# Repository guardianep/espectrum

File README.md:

# Spectre Audio Mixer

A USB audio mixer PCB with per-app volume control. Link any three applications to physical sliders and control their volume on the fly without tabbing out.

## Features

- Link any three apps to individual volume sliders
- Seamless app-to-slider mapping via desktop controller
- LED level indicators (1-10) showing current volume per slider
- OLED display showing active app mappings
- Reactive LED indicators synced to system volume
- Works in games without alt-tabbing

## Hardware Design

KiCad files available in `hardware/kicad/`:
- Schematic: `Spectre.kicad_sch`
- PCB Layout: `Spectre.kicad_pcb`

**Microcontroller:**
- ESP32-C3-DevKitM-1

**Sensors & Controls:**
- 3x Potentiometer sliders (10kΩ)
- GPIO pins 3, 4, 5 for analog input

**Output:**
- 30x SK6812MINI-E addressable RGB LEDs (10 per slider)
- SSD1306 OLED display (128x64) via I2C
- 5V and 3.3V power rails with 220µF decoupling capacitor
- 360Ω series resistors on LED data lines

**Power:**
- USB-C (5V from ESP32)
- Separate 5V rail for LEDs, 3.3V for logic

## Software

**Desktop Controller (Python):**
- Tkinter GUI for app selection
- Serial communication at 115200 baud
- Sends config format: `S1:Chrome|S2:Spotify|S3:Discord`

**Firmware (ESP32-C3):**
- Arduino framework with PlatformIO
- Adafruit NeoPixel library for LED control
- Adafruit SSD1306 library for OLED display
- Serial parsing for configuration updates

## Setup

### Hardware Assembly
1. Solder SK6812MINI-E LEDs to GPIO 0, 1, 2 (10 each)
2. Connect potentiometers to GPIO 3, 4, 5
3. Wire SSD1306 OLED via I2C (SDA, SCL)
4. Add 220µF capacitor across 5V/GND rails
5. Add 360Ω resistors on LED data lines

### Firmware
1. Install PlatformIO
2. Build and upload to ESP32-C3
3. Connect via USB (COM3 on Windows)

### Desktop App
```bash
pip install pyserial psutil
python spectre_controller.py
```

## Usage

1. Run desktop controller
2. Select apps from dropdown menus (Slider 1, 2, 3)
3. Click "Save Configuration"
4. OLED displays active app mappings
5. Move sliders to control individual app volumes
6. LED bars show volume level (1-10 LEDs lit)

## Status

- Firmware: Complete (Steps 1-4 done)
- Desktop Controller: BETA (app selection refinement in progress)
- Hardware: PCB designed, awaiting fabrication

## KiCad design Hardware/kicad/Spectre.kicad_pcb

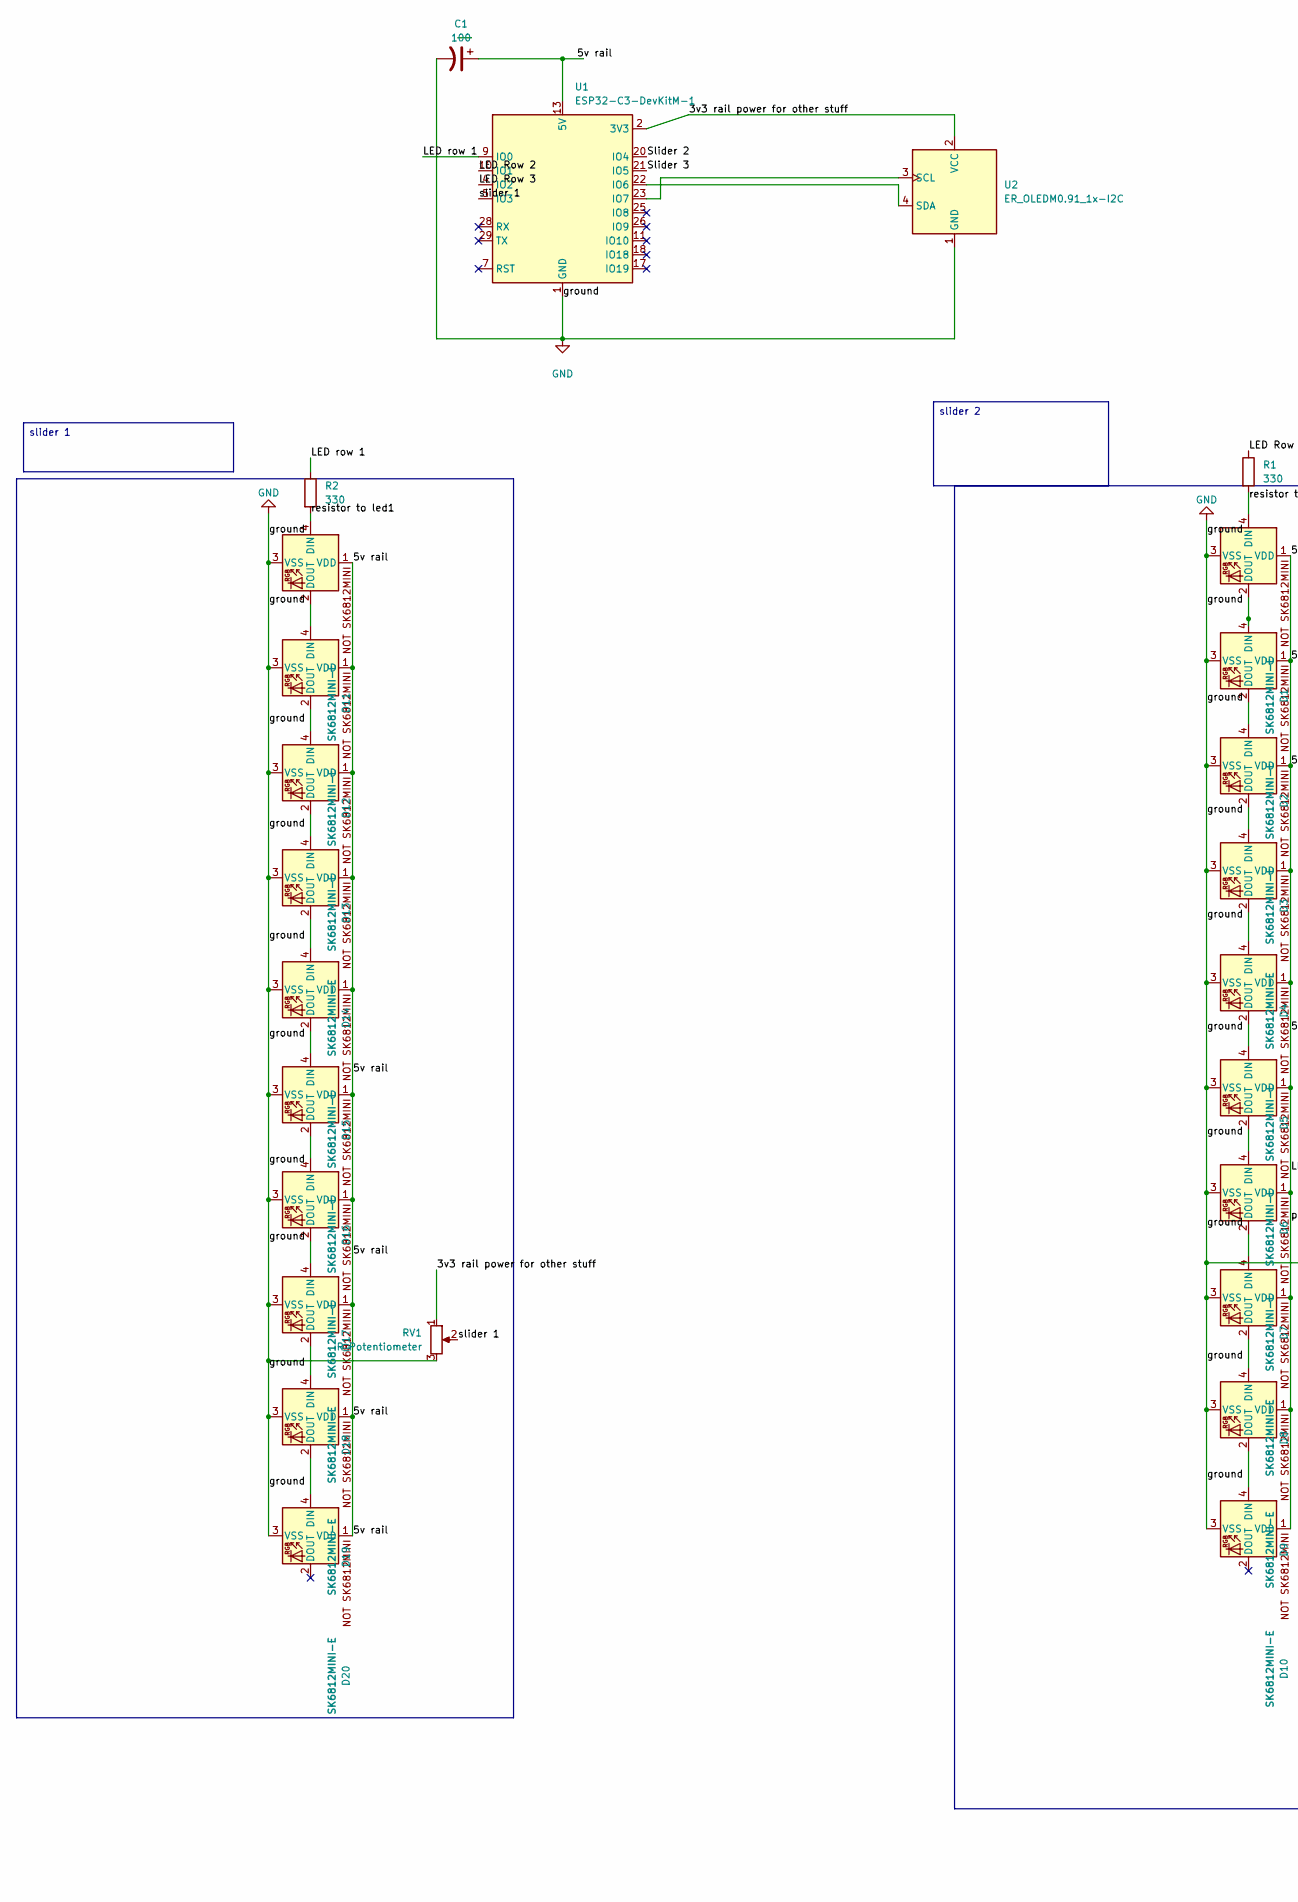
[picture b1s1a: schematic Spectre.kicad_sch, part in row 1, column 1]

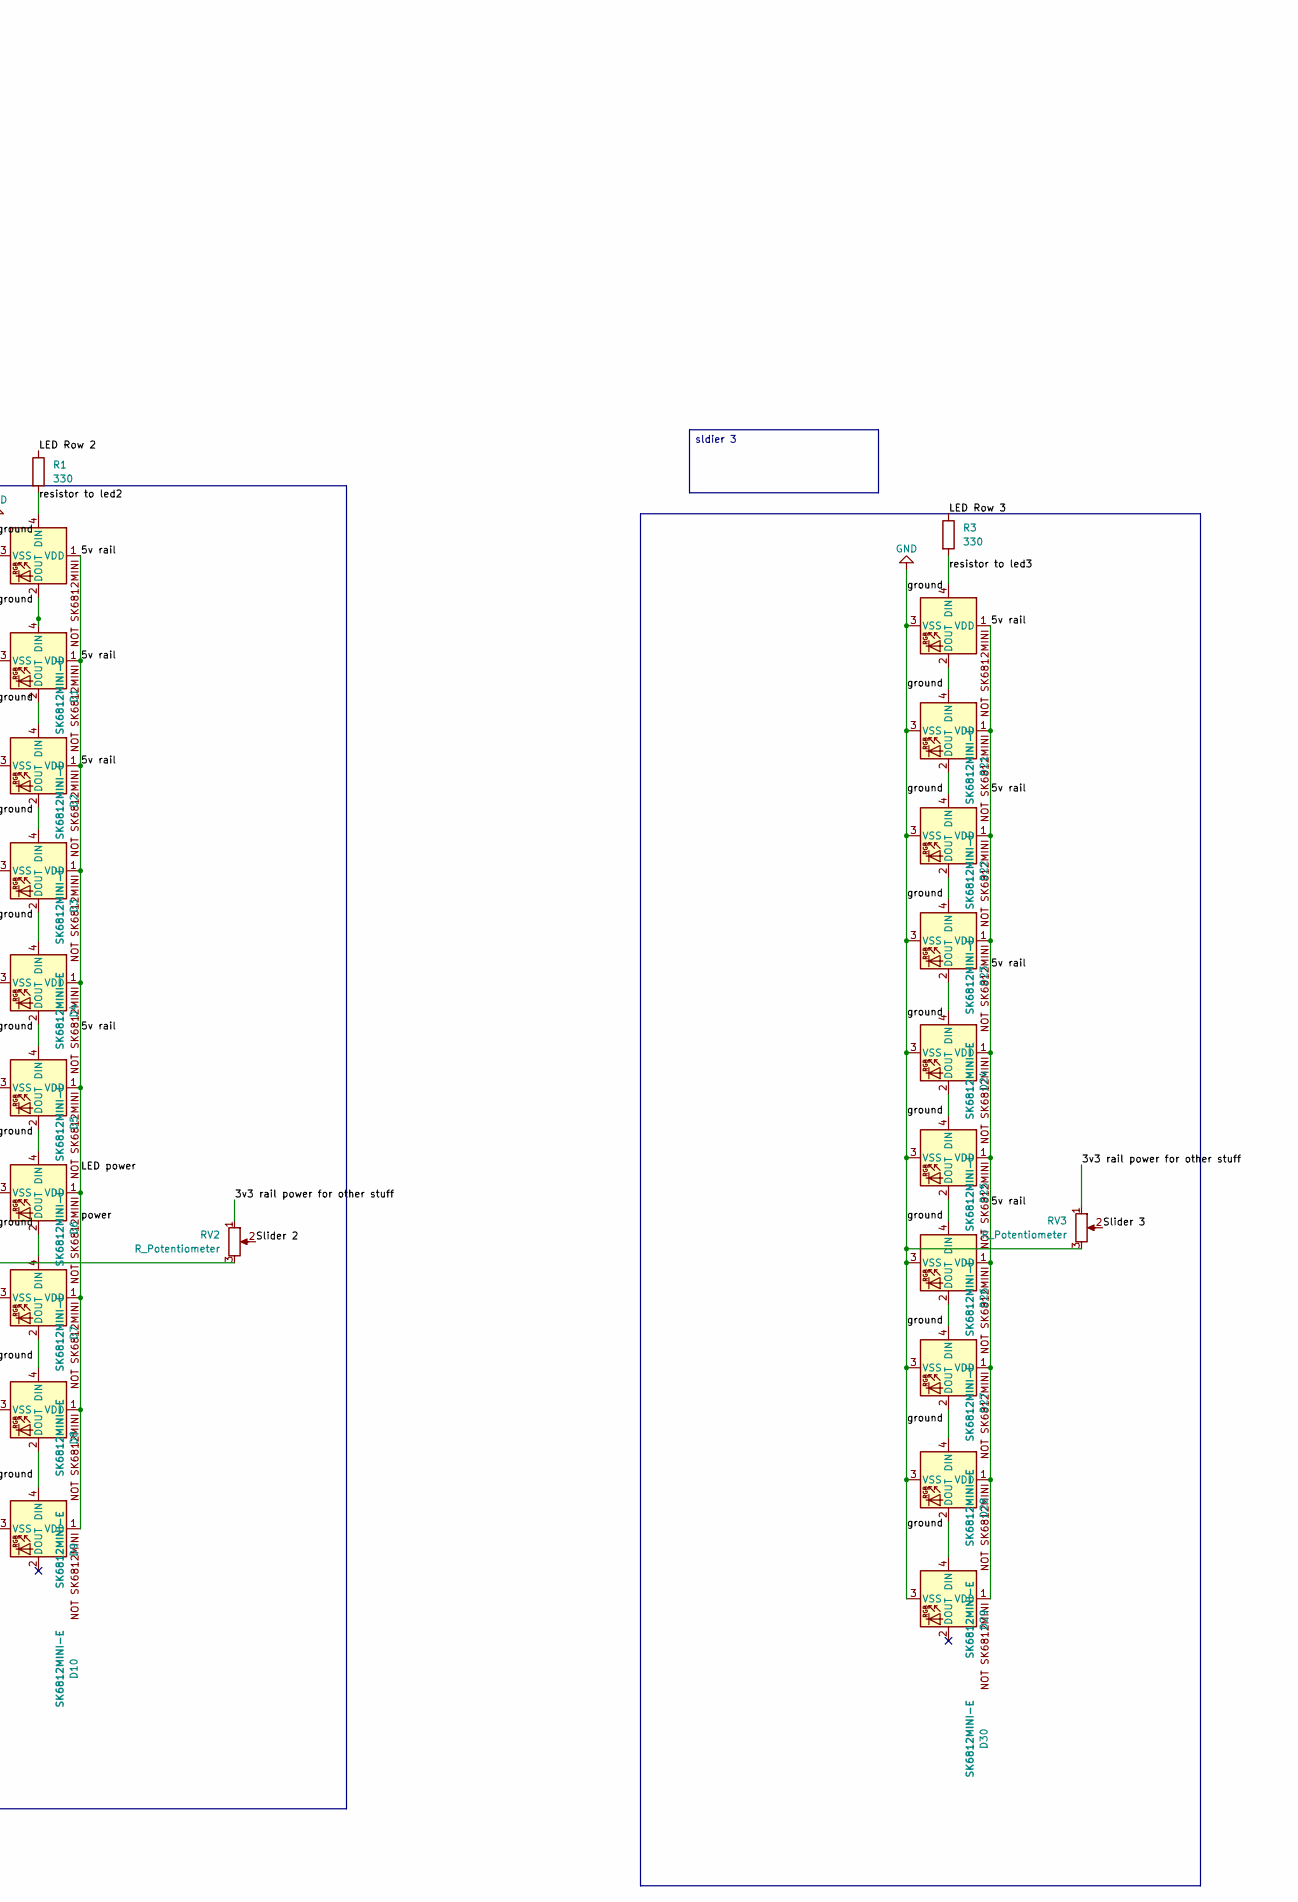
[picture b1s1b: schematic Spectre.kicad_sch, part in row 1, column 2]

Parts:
C1: 100; CP_Radial_D5.0mm_P2.00mm
D1, D2, D3, D4, D5, D6, D7, D8, D9, D10, D11, D12, D13, D14, D15, D16, D17, D18, D19, D20, D21, D22, D23, D24, D25, D26, D27, D28, D29, D30: SK6812MINI-E; SK6812MINI-E_fixed_fixed
R1, R2, R3: 330; R_Axial_DIN0207_L6.3mm_D2.5mm_P2.54mm_Vertical
RV1, RV2, RV3: R_Potentiometer; Potentiometer_Bourns_PTA3043_Single_Slide
U1: ESP32-C3-DevKitM-1; ESP32-C3-DevKitM-1-3
U2: ER_OLEDM0.91_1x-I2C; ER_OLEDM0.91_1x-I2C-new-newser

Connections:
/3v3 rail power for other stuff: RV1.1, RV2.1, RV3.1, U1.2 (3V3), U1.3 (3V3), U2.2 (VCC)
/5v rail: C1.1, D1.1 (VDD), D2.1 (VDD), D3.1 (VDD), D4.1 (VDD), D5.1 (VDD), D6.1 (VDD), D7.1 (VDD), D8.1 (VDD), D9.1 (VDD), D10.1 (VDD), D11.1 (VDD), D12.1 (VDD), D13.1 (VDD), D14.1 (VDD), D15.1 (VDD), D16.1 (VDD), D17.1 (VDD), D18.1 (VDD), D19.1 (VDD), D20.1 (VDD), D21.1 (VDD), D22.1 (VDD), D23.1 (VDD), D24.1 (VDD), D25.1 (VDD), D26.1 (VDD), D27.1 (VDD), D28.1 (VDD), D29.1 (VDD), D30.1 (VDD), U1.13 (5V), U1.14 (5V)
/LED Row 2: R1.1, U1.10 (IO1)
/LED Row 3: R3.1, U1.4 (IO2)
/LED row 1: R2.1, U1.9 (IO0)
/Slider 2: RV2.2, U1.20 (IO4)
/Slider 3: RV3.2, U1.21 (IO5)
/resistor to led1: D11.4 (DIN), R2.2
/resistor to led2: D1.4 (DIN), R1.2
/resistor to led3: D21.4 (DIN), R3.2
/slider 1: RV1.2, U1.5 (IO3)
GND: C1.2, D1.3 (VSS), D2.3 (VSS), D3.3 (VSS), D4.3 (VSS), D5.3 (VSS), D6.3 (VSS), D7.3 (VSS), D8.3 (VSS), D9.3 (VSS), D10.3 (VSS), D11.3 (VSS), D12.3 (VSS), D13.3 (VSS), D14.3 (VSS), D15.3 (VSS), D16.3 (VSS), D17.3 (VSS), D18.3 (VSS), D19.3 (VSS), D20.3 (VSS), D21.3 (VSS), D22.3 (VSS), D23.3 (VSS), D24.3 (VSS), D25.3 (VSS), D26.3 (VSS), D27.3 (VSS), D28.3 (VSS), D29.3 (VSS), D30.3 (VSS), RV1.3, RV2.3, RV3.3, U1.1 (GND), U1.6 (GND), U1.8 (GND), U1.12 (GND), U1.15 (GND), U1.16 (GND), U1.19 (GND), U1.24 (GND), U1.27 (GND), U1.30 (GND), U2.1 (GND)
unnamed: D1.2 (DOUT), D2.4 (DIN)
unnamed: D2.2 (DOUT), D3.4 (DIN)
unnamed: D3.2 (DOUT), D4.4 (DIN)
unnamed: D4.2 (DOUT), D5.4 (DIN)
unnamed: D5.2 (DOUT), D6.4 (DIN)
unnamed: D6.2 (DOUT), D7.4 (DIN)
unnamed: D7.2 (DOUT), D8.4 (DIN)
unnamed: D8.2 (DOUT), D9.4 (DIN)
unnamed: D9.2 (DOUT), D10.4 (DIN)
unnamed: D11.2 (DOUT), D12.4 (DIN)
unnamed: D12.2 (DOUT), D13.4 (DIN)
unnamed: D13.2 (DOUT), D14.4 (DIN)
unnamed: D14.2 (DOUT), D15.4 (DIN)
unnamed: D15.2 (DOUT), D16.4 (DIN)
unnamed: D16.2 (DOUT), D17.4 (DIN)
unnamed: D17.2 (DOUT), D18.4 (DIN)
unnamed: D18.2 (DOUT), D19.4 (DIN)
unnamed: D19.2 (DOUT), D20.4 (DIN)
unnamed: D21.2 (DOUT), D22.4 (DIN)
unnamed: D22.2 (DOUT), D23.4 (DIN)
unnamed: D23.2 (DOUT), D24.4 (DIN)
unnamed: D24.2 (DOUT), D25.4 (DIN)
unnamed: D25.2 (DOUT), D26.4 (DIN)
unnamed: D26.2 (DOUT), D27.4 (DIN)
unnamed: D27.2 (DOUT), D28.4 (DIN)
unnamed: D28.2 (DOUT), D29.4 (DIN)
unnamed: D29.2 (DOUT), D30.4 (DIN)
unnamed: U1.22 (IO6), U2.4 (SDA)
unnamed: U1.23 (IO7), U2.3 (SCL)

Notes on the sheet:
slider 1
sldier 3
slider 2

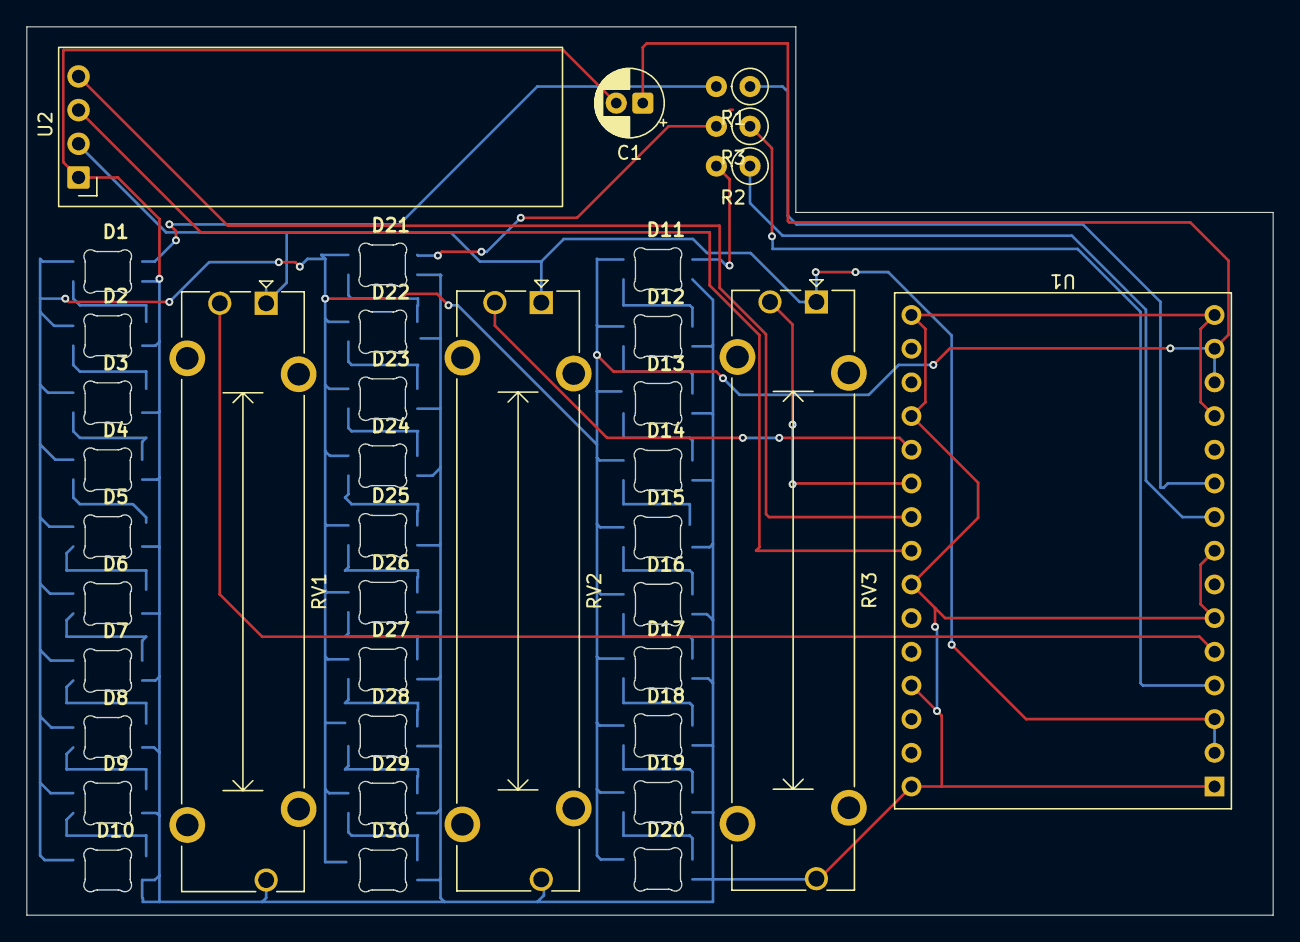
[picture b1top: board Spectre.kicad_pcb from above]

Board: 2 copper layers, 94.0 x 67.0 mm, 39 parts (0 on the bottom side), 41 nets.

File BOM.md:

# spectrum – bill of materials

<!-- Generated by Half Life from project cmuvj5xwb00d401py60ff5duv. Edits here are overwritten on the next sync. -->
<!-- Generated: 2026-10-11T03:45:46.908Z -->

> [!NOTE]
> This parts list is mirrored from [Half Life](https://halflife.hackclub.com). Editing it here will not change the platform's copy, and the next sync overwrites this file.

| Week | Tier | Parts funding |
| --- | --- | --- |
| Week 1 | Tier 2 | $65.00 |

| Part | What it's for | Qty | Unit | Total | Vendor |
| --- | --- | --- | --- | --- | --- |
| [SK6812MINI-E](https://www.aliexpress.us/item/3256808122486614.html?spm=a2g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 | RGb lighting and Volume indication, need 50 piece set | 1 | $9.15 | $9.15 | [Shenzhen Boyida Electronics Co., Ltd.](https://www.aliexpress.us/item/3256808122486614.html?spm=a2g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 |
| [ESP32-C3-DevKitM-1](https://www.aliexpress.us/item/3256806308624144.html?spm=a2g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 | Main brains of the volume thing | 1 | $9.90 | $9.90 | [Gaqqee Official Store](https://www.aliexpress.us/item/3256806308624144.html?spm=a2g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 |
| [5Pcs Straight Single Linear Slide Potentiometer](https://www.amazon.com/gp/product/B0DSQ6XD2M/ref=ox_sc_act_t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 | Linear potentiomter, used to chnage the volume of the apps based on the resistance | 1 | $8.89 | $8.89 | [MECCANIXITY](https://www.amazon.com/gp/product/B0DSQ6XD2M/ref=ox_sc_act_t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 |
| [0.91 inch OLED module](https://www.aliexpress.us/item/3256807013199079.html?spm=a2g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 | used for displaying info like app volume, which app goes with which slider, or which app's volume was chnaged | 1 | $1.09 | $1.09 | [Good Luck Electronic Productions](https://www.aliexpress.us/item/3256807013199079.html?spm=a2g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 |
| [PCB](https://cart.jlcpcb.com/quote/gerberviewThree/?qs=1a6e730dce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 | IT connectes Everythign together. | 1 | $4.00 | $4.00 | [JLCPCB](https://cart.jlcpcb.com/quote/gerberviewThree/?qs=1a6e730dce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 |
| [330 Ohm REsistors](https://www.aliexpress.us/item/3256801782956510.html?spm=a2g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"order"%3A"404"%2C"eval"%3A"1"%2C"fromPage"%3A"search"%7D&pdp_npi=6%40dis%21USD%213.03%211.09%21%21%213.03%211.09%21%402101c28d17916897674214701e0e75%2112000018268283438%21sea%21US%218278671542%21ABX%211%210%21n_tag%3A-29910%3Bd%3A6f6abd46%3Bm03_new_user%3A-29895%3BpisId%3A5000000210792318&curPageLogUid=hupHApYxs4Y5&utparam-url=scene%3Asearch%7Cquery_from%3A%7Cx_object_id%3A1005001969271262%7C_p_origin_prod%3A&search_p4p_id=202610102036072262623508593800001825265_1) | Needed for data line portectionn for LEDS | 1 | $3.03 | $3.03 | [ICGOGO Store](https://www.aliexpress.us/item/3256801782956510.html?spm=a2g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"order"%3A"404"%2C"eval"%3A"1"%2C"fromPage"%3A"search"%7D&pdp_npi=6%40dis%21USD%213.03%211.09%21%21%213.03%211.09%21%402101c28d17916897674214701e0e75%2112000018268283438%21sea%21US%218278671542%21ABX%211%210%21n_tag%3A-29910%3Bd%3A6f6abd46%3Bm03_new_user%3A-29895%3BpisId%3A5000000210792318&curPageLogUid=hupHApYxs4Y5&utparam-url=scene%3Asearch%7Cquery_from%3A%7Cx_object_id%3A1005001969271262%7C_p_origin_prod%3A&search_p4p_id=202610102036072262623508593800001825265_1) |
| [220µF Polarized capacitor](https://www.aliexpress.us/item/3256803249937258.html?spm=a2g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"order"%3A"68"%2C"eval"%3A"1"%2C"fromPage"%3A"search"%7D&pdp_npi=6%40dis%21USD%211.84%211.09%21%21%2112.25%217.25%21%402103129017916899525501011e1005%2112000025782579523%21sea%21US%218278671542%21ABX%211%210%21n_tag%3A-29910%3Bd%3A6f6abd46%3Bm03_new_user%3A-29895%3BpisId%3A5000000210792318&curPageLogUid=RUY4irG1XPXD&utparam-url=scene%3Asearch%7Cquery_from%3A%7Cx_object_id%3A1005003436252010%7C_p_origin_prod%3A) | needed to avoid voltage drops when turned on from LED's first drawing power | 1 | $1.92 | $1.92 | [Tpake Store](https://www.aliexpress.us/item/3256803249937258.html?spm=a2g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"order"%3A"68"%2C"eval"%3A"1"%2C"fromPage"%3A"search"%7D&pdp_npi=6%40dis%21USD%211.84%211.09%21%21%2112.25%217.25%21%402103129017916899525501011e1005%2112000025782579523%21sea%21US%218278671542%21ABX%211%210%21n_tag%3A-29910%3Bd%3A6f6abd46%3Bm03_new_user%3A-29895%3BpisId%3A5000000210792318&curPageLogUid=RUY4irG1XPXD&utparam-url=scene%3Asearch%7Cquery_from%3A%7Cx_object_id%3A1005003436252010%7C_p_origin_prod%3A) |
| **Parts subtotal** | — | — | — | **$37.98** | — |
| **Tax & shipping** | — | — | — | **$25.00** | — |
| **Total** | — | — | — | **$62.98** | — |

$2.02 left of the tier's funding.
